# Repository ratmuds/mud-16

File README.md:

# mud-16

a little retro console with a Motorola 68000 and FPGA PPU

# firmware

`ppu.sv` is the Verilog code for the PPU. This is close to what will be the renderer of the game console. `main.cpp` is currently a test bench that gets the display output from the PPU and renders it with Raylib, as well as simulating the CPU bus arbitration and SRAM VRAM access

# features

-   3.5" IPS Display
-   D-pad and ABXY buttons
-   27 MHz FPGA
-   Rechargable Battery
-   512 KB of SRAM

## why

I think that the GameBoy and other retro game console are really cool, and I want to make my own console. But I didn't want to just emulate it, I wanted to use a real retro CPU and make my own PPU (picture processing unit) with a FPGA.

## how

The CPU is the brain pretty much. It handles all the game logic and stuff. It's connected to 512 KB of SRAM which the first part of it is allocated to VRAM. The VRAM is used by the FPGA. The CPU needs to go through level shifters down to 3.3V, and the CPU and FPGA needs to handle bus arbitration properly, otherwise they will fight over the bus and everything will become a mess. The FPGA will request for the bus at the beginning of each frame where they will essentially perform a handshake and the bus will be passed to the FPGA. The FPGA then accesses all the VRAM it needs and then gives back control to the CPU.

The display will be running in 8 bit parallel mode, since SPI is too slow.

## to use

this stuff is WIP

you'll need to flash everything to the FPGA which will load all the necessary data into RAM for the CPU. The Gowin IDE is the app you'll use to flash the Tang Nano.

# Schematic screenshots

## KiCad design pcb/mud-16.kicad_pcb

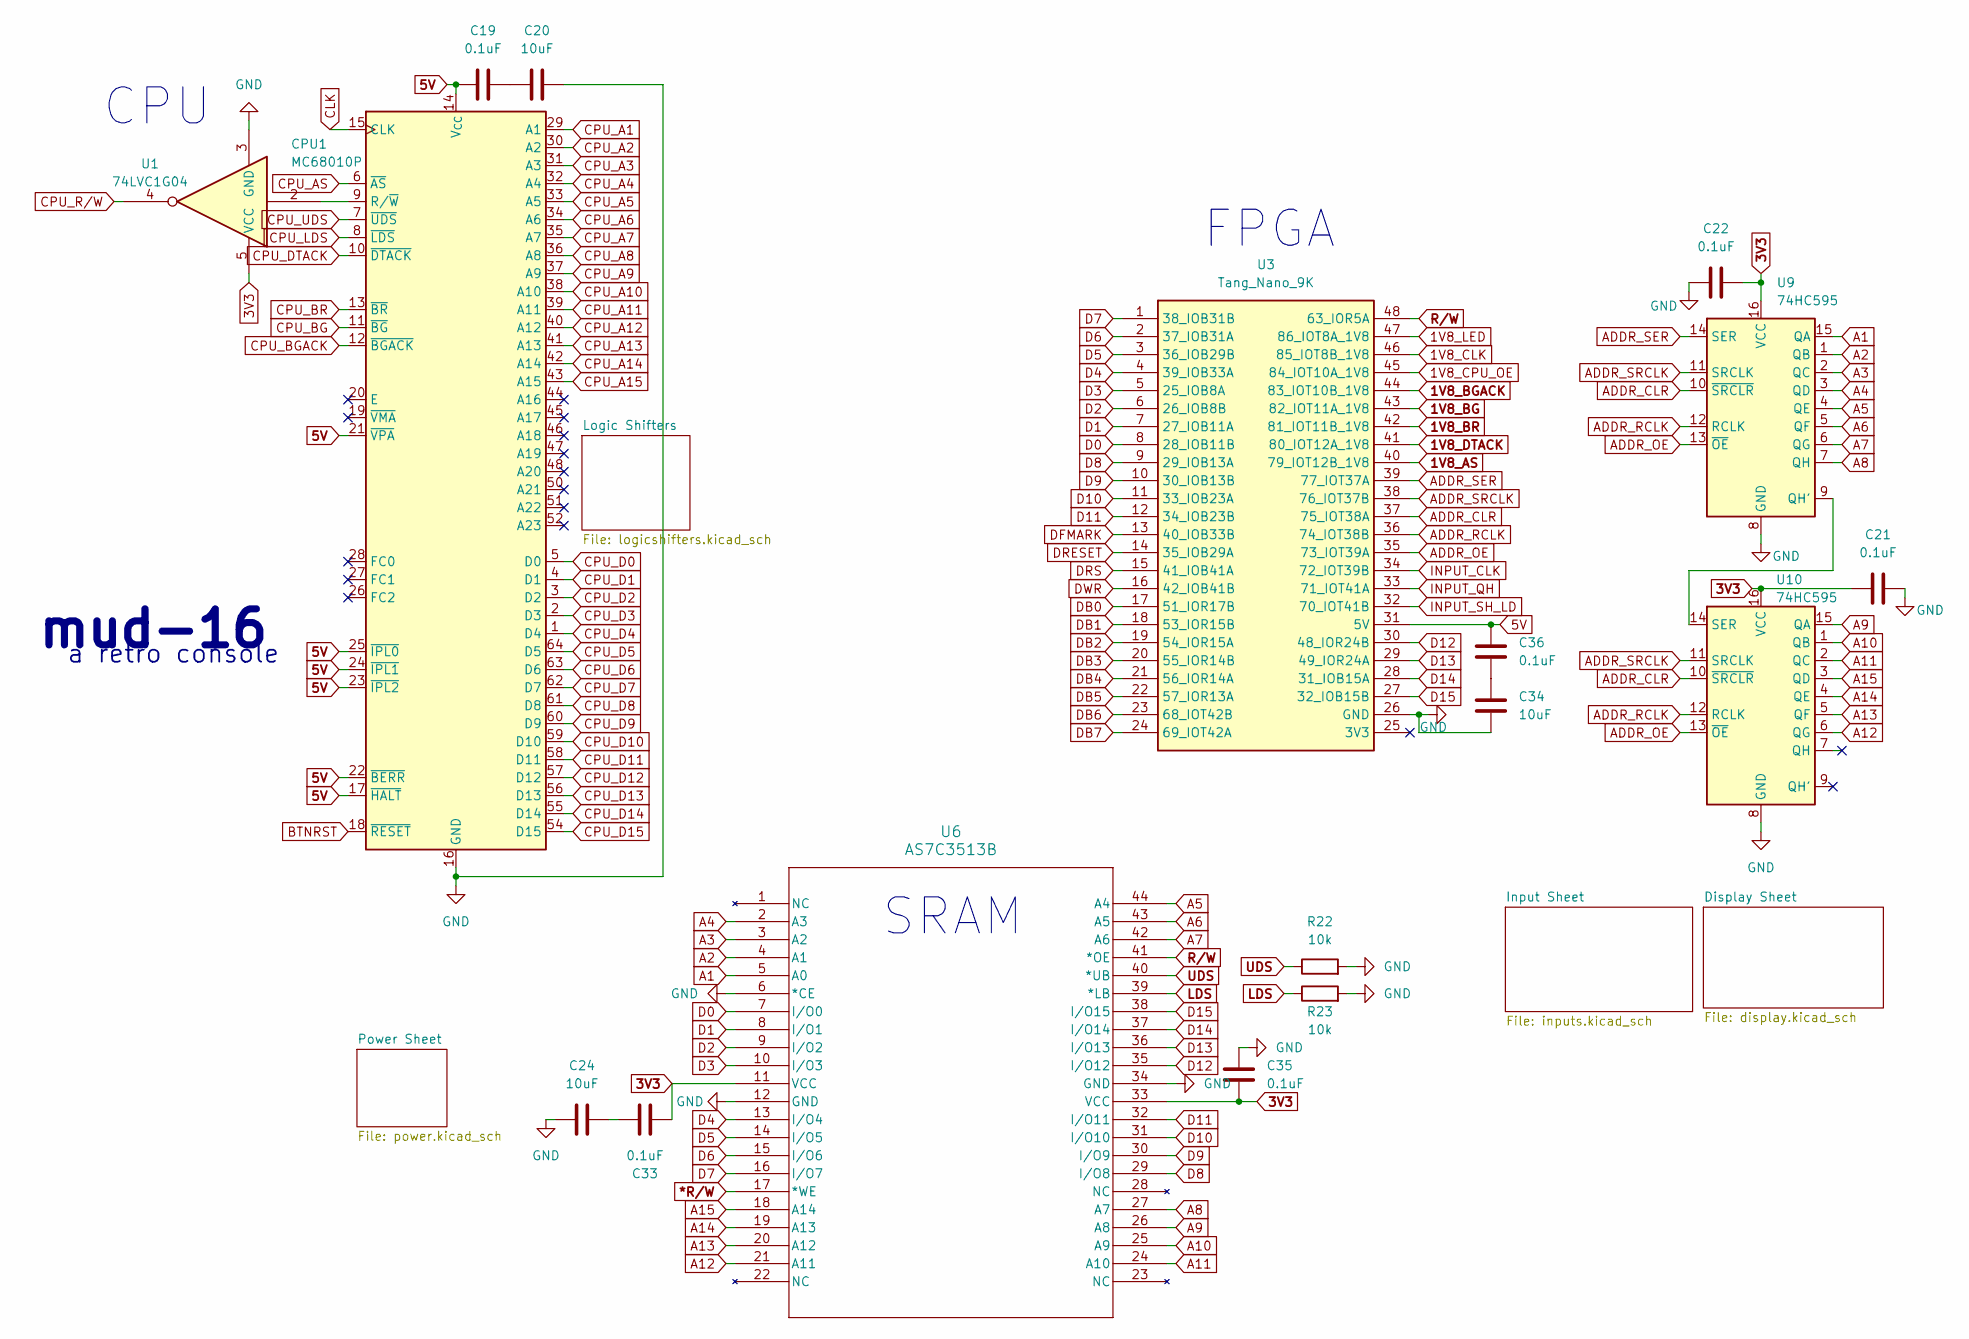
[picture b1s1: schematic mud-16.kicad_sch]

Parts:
C19, C21, C22, C33, C35, C36: 0.1uF; C_0805_2012Metric_Pad1.18x1.45mm_HandSolder
C20, C24, C34: 10uF; C_0805_2012Metric_Pad1.18x1.45mm_HandSolder
CPU1: MC68010P; DIP-64_W22.86mm
R22, R23: 10k; R_0805_2012Metric_Pad1.20x1.40mm_HandSolder
U1: 74LVC1G04; SOT-23-5_HandSoldering
U3: Tang_Nano_9K; DIP-48_TangNano9K
U6: AS7C3513B; TSOP-44_10P2X18P4_ALL
U9, U10: 74HC595; SOIC-16_3.9x9.9mm_P1.27mm

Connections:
1V8_AS: U3.40 (79_IOT12B_1V8); also elsewhere on the board
1V8_BG: U3.43 (82_IOT11A_1V8); also elsewhere on the board
1V8_BGACK: U3.44 (83_IOT10B_1V8); also elsewhere on the board
1V8_BR: U3.42 (81_IOT11B_1V8); also elsewhere on the board
1V8_CLK: U3.46 (85_IOT8B_1V8); also elsewhere on the board
1V8_CPU_OE: U3.45 (84_IOT10A_1V8); also elsewhere on the board
1V8_DTACK: U3.41 (80_IOT12A_1V8); also elsewhere on the board
1V8_LED: U3.47 (86_IOT8A_1V8); also elsewhere on the board
3V3: C21.1, C22.2, C33.1, C35.2, U1.5 (VCC), U6.11 (VCC), U6.33 (VCC), U9.16 (VCC), U10.16 (VCC); also elsewhere on the board
5V: C19.1, C36.1, CPU1.14 (V_{CC}), CPU1.17 (~HALT), CPU1.21 (~VPA), CPU1.22 (~BERR), CPU1.23 (~IPL2), CPU1.24 (~IPL1), CPU1.25 (~IPL0), CPU1.49 (V_{CC}), U3.31 (5V); also elsewhere on the board
*R/W: U6.17 (*WE); also elsewhere on the board
A1: U6.5 (A0), U9.15 (QA); also elsewhere on the board
A2: U6.4 (A1), U9.1 (QB); also elsewhere on the board
A3: U6.3 (A2), U9.2 (QC); also elsewhere on the board
A4: U6.2 (A3), U9.3 (QD); also elsewhere on the board
A5: U6.44 (A4), U9.4 (QE); also elsewhere on the board
A6: U6.43 (A5), U9.5 (QF); also elsewhere on the board
A7: U6.42 (A6), U9.6 (QG); also elsewhere on the board
A8: U6.27 (A7), U9.7 (QH); also elsewhere on the board
A9: U6.26 (A8), U10.15 (QA); also elsewhere on the board
A10: U6.25 (A9), U10.1 (QB); also elsewhere on the board
A11: U6.24 (A10), U10.2 (QC); also elsewhere on the board
A12: U6.21 (A11), U10.6 (QG); also elsewhere on the board
A13: U6.20 (A12), U10.5 (QF); also elsewhere on the board
A14: U6.19 (A13), U10.4 (QE); also elsewhere on the board
A15: U6.18 (A14), U10.3 (QD); also elsewhere on the board
ADDR_CLR: U3.37 (75_IOT38A), U9.10 (~SRCLR), U10.10 (~SRCLR)
ADDR_OE: U3.35 (73_IOT39A), U9.13 (~OE), U10.13 (~OE)
ADDR_RCLK: U3.36 (74_IOT38B), U9.12 (RCLK), U10.12 (RCLK)
ADDR_SER: U3.39 (77_IOT37A), U9.14 (SER)
ADDR_SRCLK: U3.38 (76_IOT37B), U9.11 (SRCLK), U10.11 (SRCLK)
BTNRST: CPU1.18 (~RESET); also elsewhere on the board
CLK: CPU1.15 (CLK); also elsewhere on the board
CPU_A1: CPU1.29 (A1); also elsewhere on the board
CPU_A2: CPU1.30 (A2); also elsewhere on the board
CPU_A3: CPU1.31 (A3); also elsewhere on the board
CPU_A4: CPU1.32 (A4); also elsewhere on the board
CPU_A5: CPU1.33 (A5); also elsewhere on the board
CPU_A6: CPU1.34 (A6); also elsewhere on the board
CPU_A7: CPU1.35 (A7); also elsewhere on the board
CPU_A8: CPU1.36 (A8); also elsewhere on the board
CPU_A9: CPU1.37 (A9); also elsewhere on the board
CPU_A10: CPU1.38 (A10); also elsewhere on the board
CPU_A11: CPU1.39 (A11); also elsewhere on the board
CPU_A12: CPU1.40 (A12); also elsewhere on the board
CPU_A13: CPU1.41 (A13); also elsewhere on the board
CPU_A14: CPU1.42 (A14); also elsewhere on the board
CPU_A15: CPU1.43 (A15); also elsewhere on the board
CPU_AS: CPU1.6 (~AS); also elsewhere on the board
CPU_BG: CPU1.11 (~BG); also elsewhere on the board
CPU_BGACK: CPU1.12 (~BGACK); also elsewhere on the board
CPU_BR: CPU1.13 (~BR); also elsewhere on the board
CPU_D0: CPU1.5 (D0); also elsewhere on the board
CPU_D1: CPU1.4 (D1); also elsewhere on the board
CPU_D2: CPU1.3 (D2); also elsewhere on the board
CPU_D3: CPU1.2 (D3); also elsewhere on the board
CPU_D4: CPU1.1 (D4); also elsewhere on the board
CPU_D5: CPU1.64 (D5); also elsewhere on the board
CPU_D6: CPU1.63 (D6); also elsewhere on the board
CPU_D7: CPU1.62 (D7); also elsewhere on the board
CPU_D8: CPU1.61 (D8); also elsewhere on the board
CPU_D9: CPU1.60 (D9); also elsewhere on the board
CPU_D10: CPU1.59 (D10); also elsewhere on the board
CPU_D11: CPU1.58 (D11); also elsewhere on the board
CPU_D12: CPU1.57 (D12); also elsewhere on the board
CPU_D13: CPU1.56 (D13); also elsewhere on the board
CPU_D14: CPU1.55 (D14); also elsewhere on the board
CPU_D15: CPU1.54 (D15); also elsewhere on the board
CPU_DTACK: CPU1.10 (~DTACK); also elsewhere on the board
CPU_LDS: CPU1.8 (~LDS); also elsewhere on the board
CPU_R/W: U1.4; also elsewhere on the board
CPU_UDS: CPU1.7 (~UDS); also elsewhere on the board
D0: U3.8 (28_IOB11B), U6.7 (I/O0); also elsewhere on the board
D1: U3.7 (27_IOB11A), U6.8 (I/O1); also elsewhere on the board
D2: U3.6 (26_IOB8B), U6.9 (I/O2); also elsewhere on the board
D3: U3.5 (25_IOB8A), U6.10 (I/O3); also elsewhere on the board
D4: U3.4 (39_IOB33A), U6.13 (I/O4); also elsewhere on the board
D5: U3.3 (36_IOB29B), U6.14 (I/O5); also elsewhere on the board
D6: U3.2 (37_IOB31A), U6.15 (I/O6); also elsewhere on the board
D7: U3.1 (38_IOB31B), U6.16 (I/O7); also elsewhere on the board
D8: U3.9 (29_IOB13A), U6.29 (I/O8); also elsewhere on the board
D9: U3.10 (30_IOB13B), U6.30 (I/O9); also elsewhere on the board
D10: U3.11 (33_IOB23A), U6.31 (I/O10); also elsewhere on the board
D11: U3.12 (34_IOB23B), U6.32 (I/O11); also elsewhere on the board
D12: U3.30 (48_IOR24B), U6.35 (I/O12); also elsewhere on the board
D13: U3.29 (49_IOR24A), U6.36 (I/O13); also elsewhere on the board
D14: U3.28 (31_IOB15A), U6.37 (I/O14); also elsewhere on the board
D15: U3.27 (32_IOB15B), U6.38 (I/O15); also elsewhere on the board
DB0: U3.17 (51_IOR17B); also elsewhere on the board
DB1: U3.18 (53_IOR15B); also elsewhere on the board
DB2: U3.19 (54_IOR15A); also elsewhere on the board
DB3: U3.20 (55_IOR14B); also elsewhere on the board
DB4: U3.21 (56_IOR14A); also elsewhere on the board
DB5: U3.22 (57_IOR13A); also elsewhere on the board
DB6: U3.23 (68_IOT42B); also elsewhere on the board
DB7: U3.24 (69_IOT42A); also elsewhere on the board
DFMARK: U3.13 (40_IOB33B); also elsewhere on the board
DRESET: U3.14 (35_IOB29A); also elsewhere on the board
DRS: U3.15 (41_IOB41A); also elsewhere on the board
DWR: U3.16 (42_IOB41B); also elsewhere on the board
GND: C20.2, C21.2, C22.1, C24.1, C34.2, C35.1, CPU1.16 (GND), CPU1.53 (GND), R22.2, R23.2, U1.3 (GND), U3.26 (GND), U6.6 (*CE), U6.12 (GND), U6.34 (GND), U9.8 (GND), U10.8 (GND); also elsewhere on the board
INPUT_CLK: U3.34 (72_IOT39B); also elsewhere on the board
INPUT_QH: U3.33 (71_IOT41A); also elsewhere on the board
INPUT_SH_LD: U3.32 (70_IOT41B); also elsewhere on the board
LDS: R23.1, U6.39 (*LB); also elsewhere on the board
unnamed: C19.2, C20.1
unnamed: C24.2, C33.2
unnamed: C34.1, C36.2
unnamed: CPU1.9 (R/~W), U1.2
unnamed: U9.9 (QH'), U10.14 (SER)
R/W: U3.48 (63_IOR5A), U6.41 (*OE); also elsewhere on the board
UDS: R22.1, U6.40 (*UB); also elsewhere on the board

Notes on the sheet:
mud-16
SRAM
FPGA
a retro console
CPU

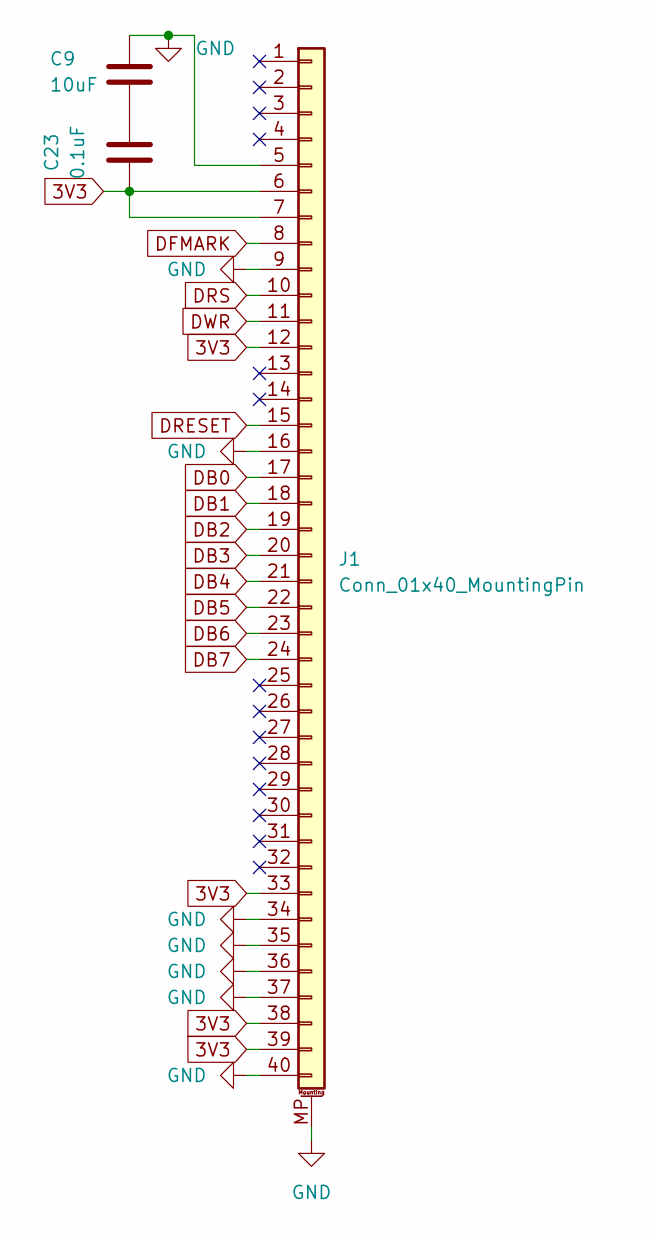
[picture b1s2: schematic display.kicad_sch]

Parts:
C9: 10uF; C_0805_2012Metric_Pad1.18x1.45mm_HandSolder
C23: 0.1uF; C_0805_2012Metric_Pad1.18x1.45mm_HandSolder
J1: Conn_01x40_MountingPin; Amphenol_F32R-1A7x1-11040_1x40-1MP_P0.5mm_Horizontal

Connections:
3V3: C23.1, J1.6, J1.7, J1.12, J1.33, J1.38, J1.39; also elsewhere on the board
DB0: J1.17; also elsewhere on the board
DB1: J1.18; also elsewhere on the board
DB2: J1.19; also elsewhere on the board
DB3: J1.20; also elsewhere on the board
DB4: J1.21; also elsewhere on the board
DB5: J1.22; also elsewhere on the board
DB6: J1.23; also elsewhere on the board
DB7: J1.24; also elsewhere on the board
DFMARK: J1.8; also elsewhere on the board
DRESET: J1.15; also elsewhere on the board
DRS: J1.10; also elsewhere on the board
DWR: J1.11; also elsewhere on the board
GND: C9.1, J1.5, J1.9, J1.16, J1.34, J1.35, J1.36, J1.37, J1.40, J1.MP (MountPin); also elsewhere on the board
unnamed: C9.2, C23.2

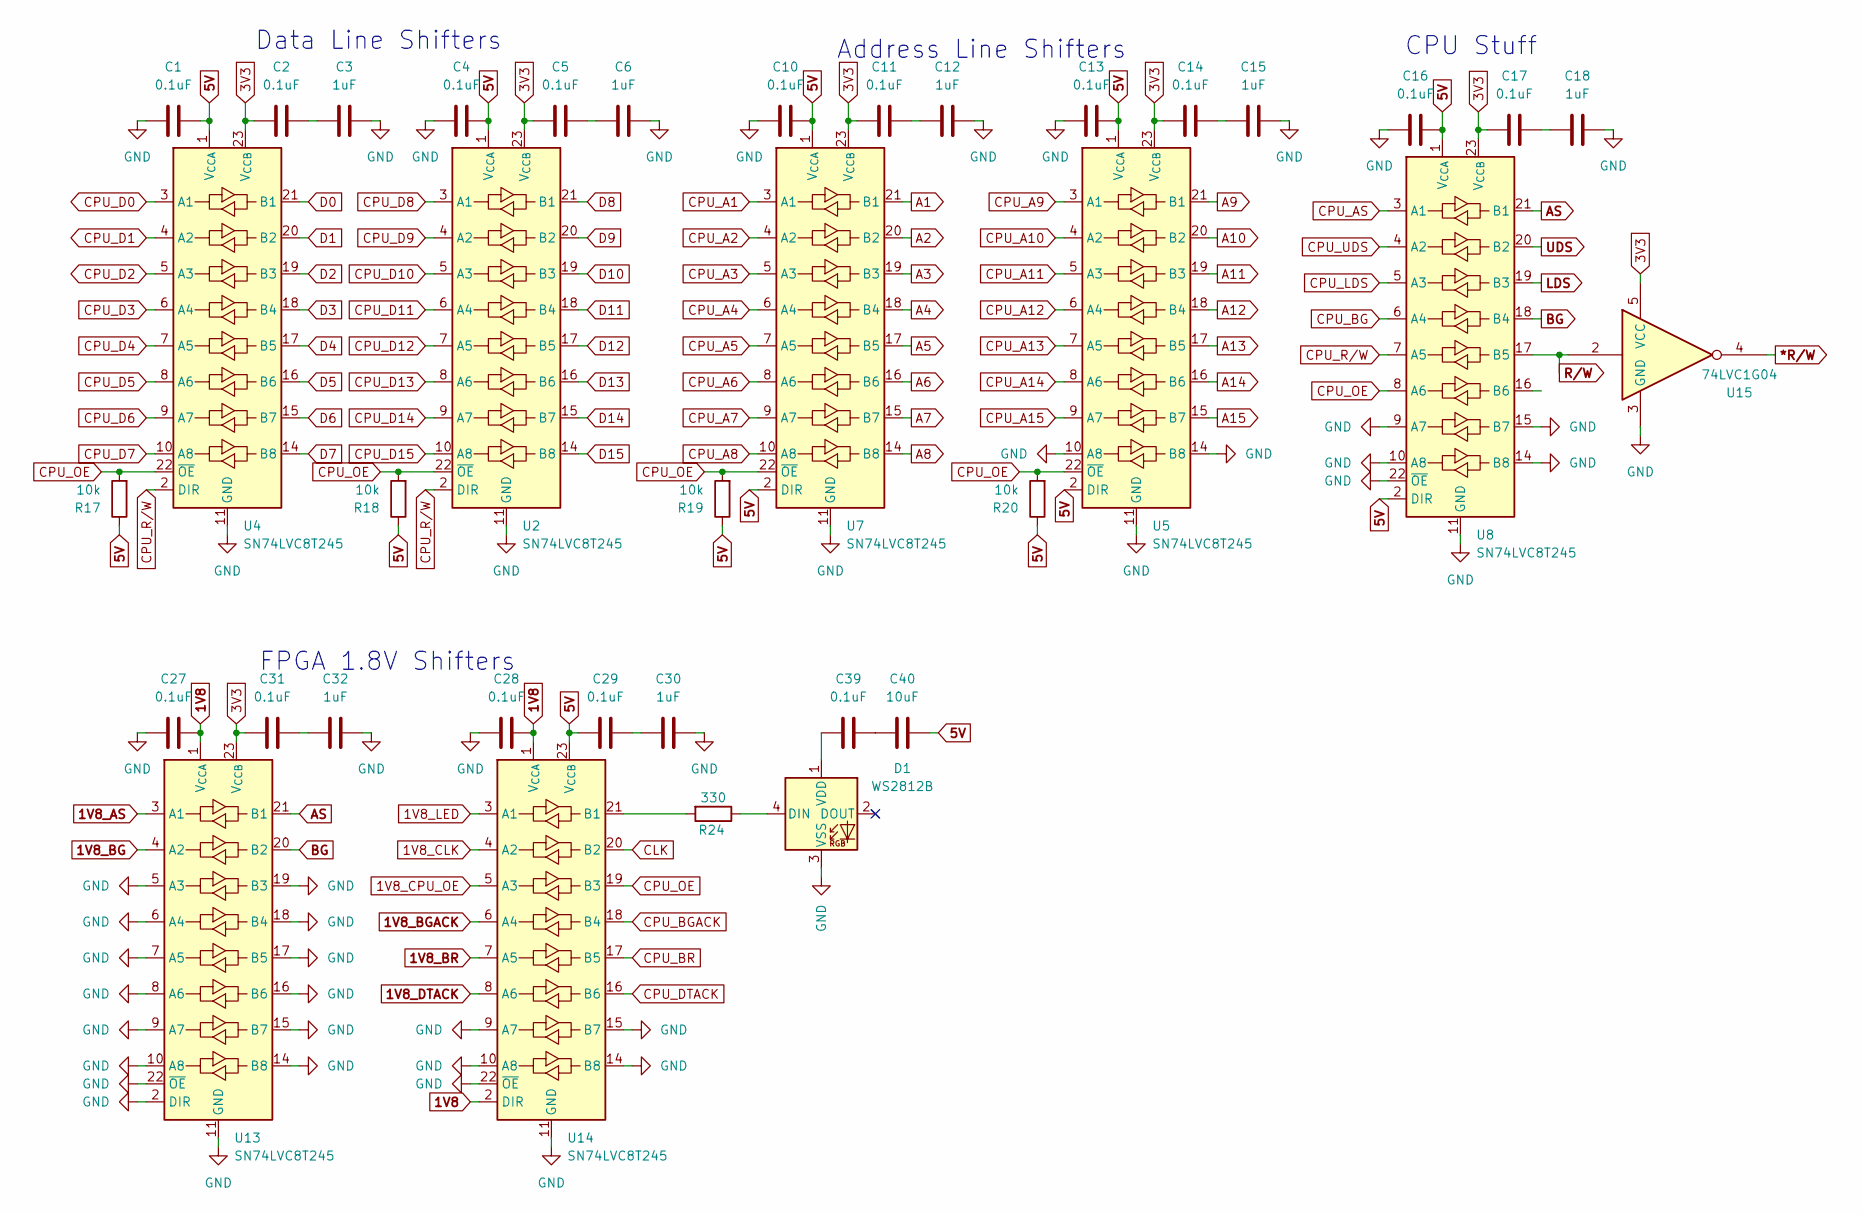
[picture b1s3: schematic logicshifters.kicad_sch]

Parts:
C1, C2, C4, C5, C10, C11, C13, C14, C16, C17, C27, C28, C29, C31, C39: 0.1uF; C_0805_2012Metric_Pad1.18x1.45mm_HandSolder
C3, C6, C12, C15, C18, C30, C32: 1uF; C_0805_2012Metric_Pad1.18x1.45mm_HandSolder
C40: 10uF; C_0805_2012Metric_Pad1.18x1.45mm_HandSolder
D1: WS2812B; LED_WS2812B_PLCC4_5.0x5.0mm_P3.2mm
R17, R18, R19, R20: 10k; R_0805_2012Metric_Pad1.20x1.40mm_HandSolder
R24: 330; R_0805_2012Metric_Pad1.20x1.40mm_HandSolder
U2, U4, U5, U7, U8, U13, U14: SN74LVC8T245; TSSOP-24_4.4x7.8mm_P0.65mm
U15: 74LVC1G04; SOT-23-5_HandSoldering

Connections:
1V8: C27.2, C28.2, U13.1 (V_{CCA}), U14.1 (V_{CCA}), U14.2 (DIR); also elsewhere on the board
1V8_AS: U13.3 (A1); also elsewhere on the board
1V8_BG: U13.4 (A2); also elsewhere on the board
1V8_BGACK: U14.6 (A4); also elsewhere on the board
1V8_BR: U14.7 (A5); also elsewhere on the board
1V8_CLK: U14.4 (A2); also elsewhere on the board
1V8_CPU_OE: U14.5 (A3); also elsewhere on the board
1V8_DTACK: U14.8 (A6); also elsewhere on the board
1V8_LED: U14.3 (A1); also elsewhere on the board
3V3: C2.1, C5.1, C11.1, C14.1, C17.1, C31.1, U2.23 (V_{CCB}), U2.24 (V_{CCB}), U4.23 (V_{CCB}), U4.24 (V_{CCB}), U5.23 (V_{CCB}), U5.24 (V_{CCB}), U7.23 (V_{CCB}), U7.24 (V_{CCB}), U8.23 (V_{CCB}), U8.24 (V_{CCB}), U13.23 (V_{CCB}), U13.24 (V_{CCB}), U15.5 (VCC); also elsewhere on the board
5V: C1.2, C4.2, C10.2, C13.2, C16.2, C29.1, C40.2, R17.1, R18.1, R19.1, R20.1, U2.1 (V_{CCA}), U4.1 (V_{CCA}), U5.1 (V_{CCA}), U5.2 (DIR), U7.1 (V_{CCA}), U7.2 (DIR), U8.1 (V_{CCA}), U8.2 (DIR), U14.23 (V_{CCB}), U14.24 (V_{CCB}); also elsewhere on the board
*R/W: U15.4; also elsewhere on the board
A1: U7.21 (B1); also elsewhere on the board
A2: U7.20 (B2); also elsewhere on the board
A3: U7.19 (B3); also elsewhere on the board
A4: U7.18 (B4); also elsewhere on the board
A5: U7.17 (B5); also elsewhere on the board
A6: U7.16 (B6); also elsewhere on the board
A7: U7.15 (B7); also elsewhere on the board
A8: U7.14 (B8); also elsewhere on the board
A9: U5.21 (B1); also elsewhere on the board
A10: U5.20 (B2); also elsewhere on the board
A11: U5.19 (B3); also elsewhere on the board
A12: U5.18 (B4); also elsewhere on the board
A13: U5.17 (B5); also elsewhere on the board
A14: U5.16 (B6); also elsewhere on the board
A15: U5.15 (B7); also elsewhere on the board
AS: U8.21 (B1), U13.21 (B1)
BG: U8.18 (B4), U13.20 (B2)
CLK: U14.20 (B2); also elsewhere on the board
CPU_A1: U7.3 (A1); also elsewhere on the board
CPU_A2: U7.4 (A2); also elsewhere on the board
CPU_A3: U7.5 (A3); also elsewhere on the board
CPU_A4: U7.6 (A4); also elsewhere on the board
CPU_A5: U7.7 (A5); also elsewhere on the board
CPU_A6: U7.8 (A6); also elsewhere on the board
CPU_A7: U7.9 (A7); also elsewhere on the board
CPU_A8: U7.10 (A8); also elsewhere on the board
CPU_A9: U5.3 (A1); also elsewhere on the board
CPU_A10: U5.4 (A2); also elsewhere on the board
CPU_A11: U5.5 (A3); also elsewhere on the board
CPU_A12: U5.6 (A4); also elsewhere on the board
CPU_A13: U5.7 (A5); also elsewhere on the board
CPU_A14: U5.8 (A6); also elsewhere on the board
CPU_A15: U5.9 (A7); also elsewhere on the board
CPU_AS: U8.3 (A1); also elsewhere on the board
CPU_BG: U8.6 (A4); also elsewhere on the board
CPU_BGACK: U14.18 (B4); also elsewhere on the board
CPU_BR: U14.17 (B5); also elsewhere on the board
CPU_D0: U4.3 (A1); also elsewhere on the board
CPU_D1: U4.4 (A2); also elsewhere on the board
CPU_D2: U4.5 (A3); also elsewhere on the board
CPU_D3: U4.6 (A4); also elsewhere on the board
CPU_D4: U4.7 (A5); also elsewhere on the board
CPU_D5: U4.8 (A6); also elsewhere on the board
CPU_D6: U4.9 (A7); also elsewhere on the board
CPU_D7: U4.10 (A8); also elsewhere on the board
CPU_D8: U2.3 (A1); also elsewhere on the board
CPU_D9: U2.4 (A2); also elsewhere on the board
CPU_D10: U2.5 (A3); also elsewhere on the board
CPU_D11: U2.6 (A4); also elsewhere on the board
CPU_D12: U2.7 (A5); also elsewhere on the board
CPU_D13: U2.8 (A6); also elsewhere on the board
CPU_D14: U2.9 (A7); also elsewhere on the board
CPU_D15: U2.10 (A8); also elsewhere on the board
CPU_DTACK: U14.16 (B6); also elsewhere on the board
CPU_LDS: U8.5 (A3); also elsewhere on the board
CPU_OE: R17.2, R18.2, R19.2, R20.2, U2.22 (~OE), U4.22 (~OE), U5.22 (~OE), U7.22 (~OE), U8.8 (A6), U14.19 (B3)
CPU_R/W: U2.2 (DIR), U4.2 (DIR), U8.7 (A5); also elsewhere on the board
CPU_UDS: U8.4 (A2); also elsewhere on the board
D0: U4.21 (B1); also elsewhere on the board
D1: U4.20 (B2); also elsewhere on the board
D2: U4.19 (B3); also elsewhere on the board
D3: U4.18 (B4); also elsewhere on the board
D4: U4.17 (B5); also elsewhere on the board
D5: U4.16 (B6); also elsewhere on the board
D6: U4.15 (B7); also elsewhere on the board
D7: U4.14 (B8); also elsewhere on the board
D8: U2.21 (B1); also elsewhere on the board
D9: U2.20 (B2); also elsewhere on the board
D10: U2.19 (B3); also elsewhere on the board
D11: U2.18 (B4); also elsewhere on the board
D12: U2.17 (B5); also elsewhere on the board
D13: U2.16 (B6); also elsewhere on the board
D14: U2.15 (B7); also elsewhere on the board
D15: U2.14 (B8); also elsewhere on the board
GND: C1.1, C3.2, C4.1, C6.2, C10.1, C12.2, C13.1, C15.2, C16.1, C18.2, C27.1, C28.1, C30.2, C32.2, D1.3 (VSS), U2.11 (GND), U2.12 (GND), U2.13 (GND), U4.11 (GND), U4.12 (GND), U4.13 (GND), U5.10 (A8), U5.11 (GND), U5.12 (GND), U5.13 (GND), U5.14 (B8), U7.11 (GND), U7.12 (GND), U7.13 (GND), U8.9 (A7), U8.10 (A8), U8.11 (GND), U8.12 (GND), U8.13 (GND), U8.14 (B8), U8.15 (B7), U8.22 (~OE), U13.2 (DIR), U13.5 (A3), U13.6 (A4), U13.7 (A5), U13.8 (A6), U13.9 (A7), U13.10 (A8), U13.11 (GND), U13.12 (GND), U13.13 (GND), U13.14 (B8), U13.15 (B7), U13.16 (B6), U13.17 (B5), U13.18 (B4), U13.19 (B3), U13.22 (~OE), U14.9 (A7), U14.10 (A8), U14.11 (GND), U14.12 (GND), U14.13 (GND), U14.14 (B8), U14.15 (B7), U14.22 (~OE), U15.3 (GND); also elsewhere on the board
LDS: U8.19 (B3); also elsewhere on the board
unnamed: C2.2, C3.1
unnamed: C5.2, C6.1
unnamed: C11.2, C12.1
unnamed: C14.2, C15.1
unnamed: C17.2, C18.1
unnamed: C29.2, C30.1
unnamed: C31.2, C32.1
unnamed: C39.2, C40.1
unnamed: D1.4 (DIN), R24.1
unnamed: C39.1, D1.1 (VDD)
unnamed: R24.2, U14.21 (B1)
R/W: U8.17 (B5), U15.2; also elsewhere on the board
UDS: U8.20 (B2); also elsewhere on the board

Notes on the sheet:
CPU Stuff
Data Line Shifters
FPGA 1.8V Shifters
Address Line Shifters

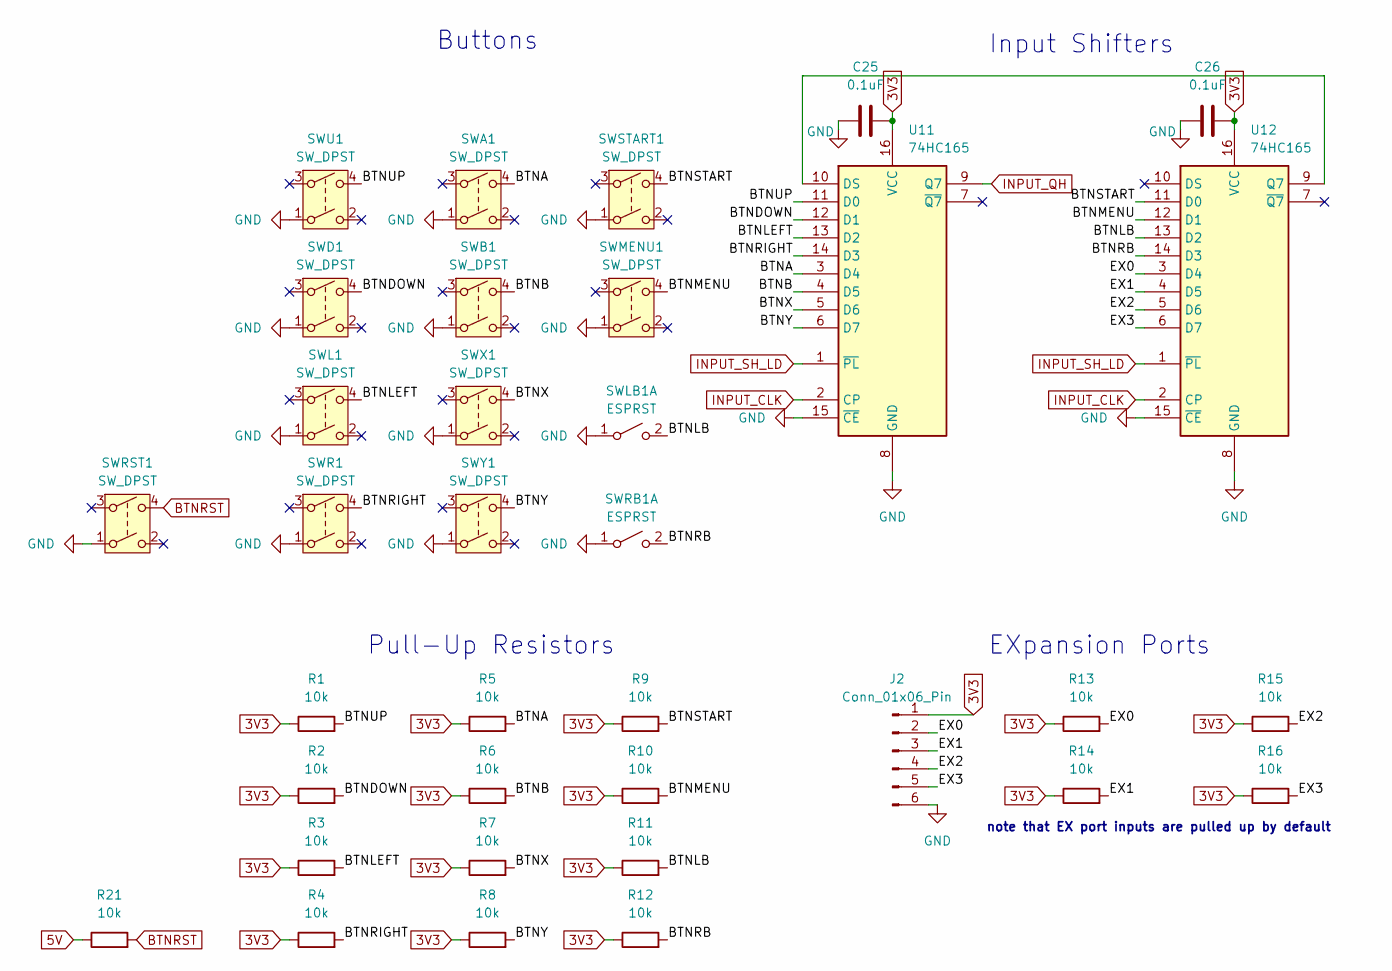
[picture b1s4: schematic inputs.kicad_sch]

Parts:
C25, C26: 0.1uF; C_0805_2012Metric_Pad1.18x1.45mm_HandSolder
J2: Conn_01x06_Pin; PinSocket_1x06_P2.54mm_Vertical
R1, R2, R3, R4, R5, R6, R7, R8, R9, R10, R11, R12, R13, R14, R15, R16, R21: 10k; R_0805_2012Metric_Pad1.20x1.40mm_HandSolder
SWA1: SW_DPST; SW_PUSH_6mm
SWB1: SW_DPST; SW_PUSH_6mm
SWD1: SW_DPST; SW_PUSH_6mm
SWL1: SW_DPST; SW_PUSH_6mm
SWLB1: ESPRST; SW_SIDE_PUSH_3x6mm
SWMENU1: SW_DPST; SW_PUSH_6mm
SWR1: SW_DPST; SW_PUSH_6mm
SWRB1: ESPRST; SW_SIDE_PUSH_3x6mm
SWRST1: SW_DPST; SW_PUSH_6mm
SWSTART1: SW_DPST; SW_PUSH_6mm
SWU1: SW_DPST; SW_PUSH_6mm
SWX1: SW_DPST; SW_PUSH_6mm
SWY1: SW_DPST; SW_PUSH_6mm
U11, U12: 74HC165; DIP-16_W7.62mm

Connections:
3V3: C25.2, C26.2, J2.1, R1.1, R2.1, R3.1, R4.1, R5.1, R6.1, R7.1, R8.1, R9.1, R10.1, R11.1, R12.1, R13.1, R14.1, R15.1, R16.1, U11.16 (VCC), U12.16 (VCC); also elsewhere on the board
5V: R21.1; also elsewhere on the board
/Input Sheet/BTNA: R5.2, SWA1.4, U11.3 (D4)
/Input Sheet/BTNB: R6.2, SWB1.4, U11.4 (D5)
/Input Sheet/BTNDOWN: R2.2, SWD1.4, U11.12 (D1)
/Input Sheet/BTNLB: R11.2, SWLB1.2 (B), U12.13 (D2)
/Input Sheet/BTNLEFT: R3.2, SWL1.4, U11.13 (D2)
/Input Sheet/BTNMENU: R10.2, SWMENU1.4, U12.12 (D1)
/Input Sheet/BTNRB: R12.2, SWRB1.2 (B), U12.14 (D3)
/Input Sheet/BTNRIGHT: R4.2, SWR1.4, U11.14 (D3)
/Input Sheet/BTNSTART: R9.2, SWSTART1.4, U12.11 (D0)
/Input Sheet/BTNUP: R1.2, SWU1.4, U11.11 (D0)
/Input Sheet/BTNX: R7.2, SWX1.4, U11.5 (D6)
/Input Sheet/BTNY: R8.2, SWY1.4, U11.6 (D7)
/Input Sheet/EX0: J2.2, R13.2, U12.3 (D4)
/Input Sheet/EX1: J2.3, R14.2, U12.4 (D5)
/Input Sheet/EX2: J2.4, R15.2, U12.5 (D6)
/Input Sheet/EX3: J2.5, R16.2, U12.6 (D7)
BTNRST: R21.2, SWRST1.4; also elsewhere on the board
GND: C25.1, C26.1, J2.6, SWA1.1, SWB1.1, SWD1.1, SWL1.1, SWLB1.1 (A), SWMENU1.1, SWR1.1, SWRB1.1 (A), SWRST1.1, SWSTART1.1, SWU1.1, SWX1.1, SWY1.1, U11.8 (GND), U11.15 (~CE), U12.8 (GND), U12.15 (~CE); also elsewhere on the board
INPUT_CLK: U11.2 (CP), U12.2 (CP); also elsewhere on the board
INPUT_QH: U11.9 (Q7); also elsewhere on the board
INPUT_SH_LD: U11.1 (~PL), U12.1 (~PL); also elsewhere on the board
unnamed: U11.10 (DS), U12.9 (Q7)

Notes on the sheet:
Pull-Up Resistors
EXpansion Ports
note that EX port inputs are pulled up by default
Buttons
Input Shifters

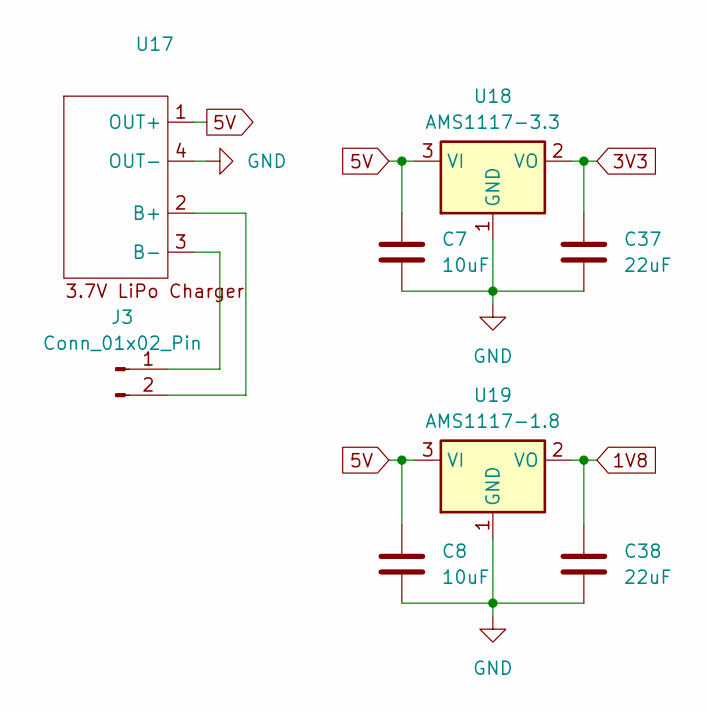
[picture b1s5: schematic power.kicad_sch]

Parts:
C7, C8: 10uF; C_0805_2012Metric_Pad1.18x1.45mm_HandSolder
C37, C38: 22uF; C_0805_2012Metric_Pad1.18x1.45mm_HandSolder
J3: Conn_01x02_Pin; JST_PH_S2B-PH-K_1x02_P2.00mm_Horizontal
U17: 3.7V_LiPo_Charging_Board
U18: AMS1117-3.3; SOT-223-3_TabPin2
U19: AMS1117-1.8; SOT-223-3_TabPin2

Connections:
1V8: C38.1, U19.2 (VO); also elsewhere on the board
3V3: C37.1, U18.2 (VO); also elsewhere on the board
5V: C7.1, C8.1, U17.1 (OUT+), U18.3 (VI), U19.3 (VI); also elsewhere on the board
GND: C7.2, C8.2, C37.2, C38.2, U17.4 (OUT-), U18.1 (GND), U19.1 (GND); also elsewhere on the board
unnamed: J3.1, U17.3 (B-)
unnamed: J3.2, U17.2 (B+)

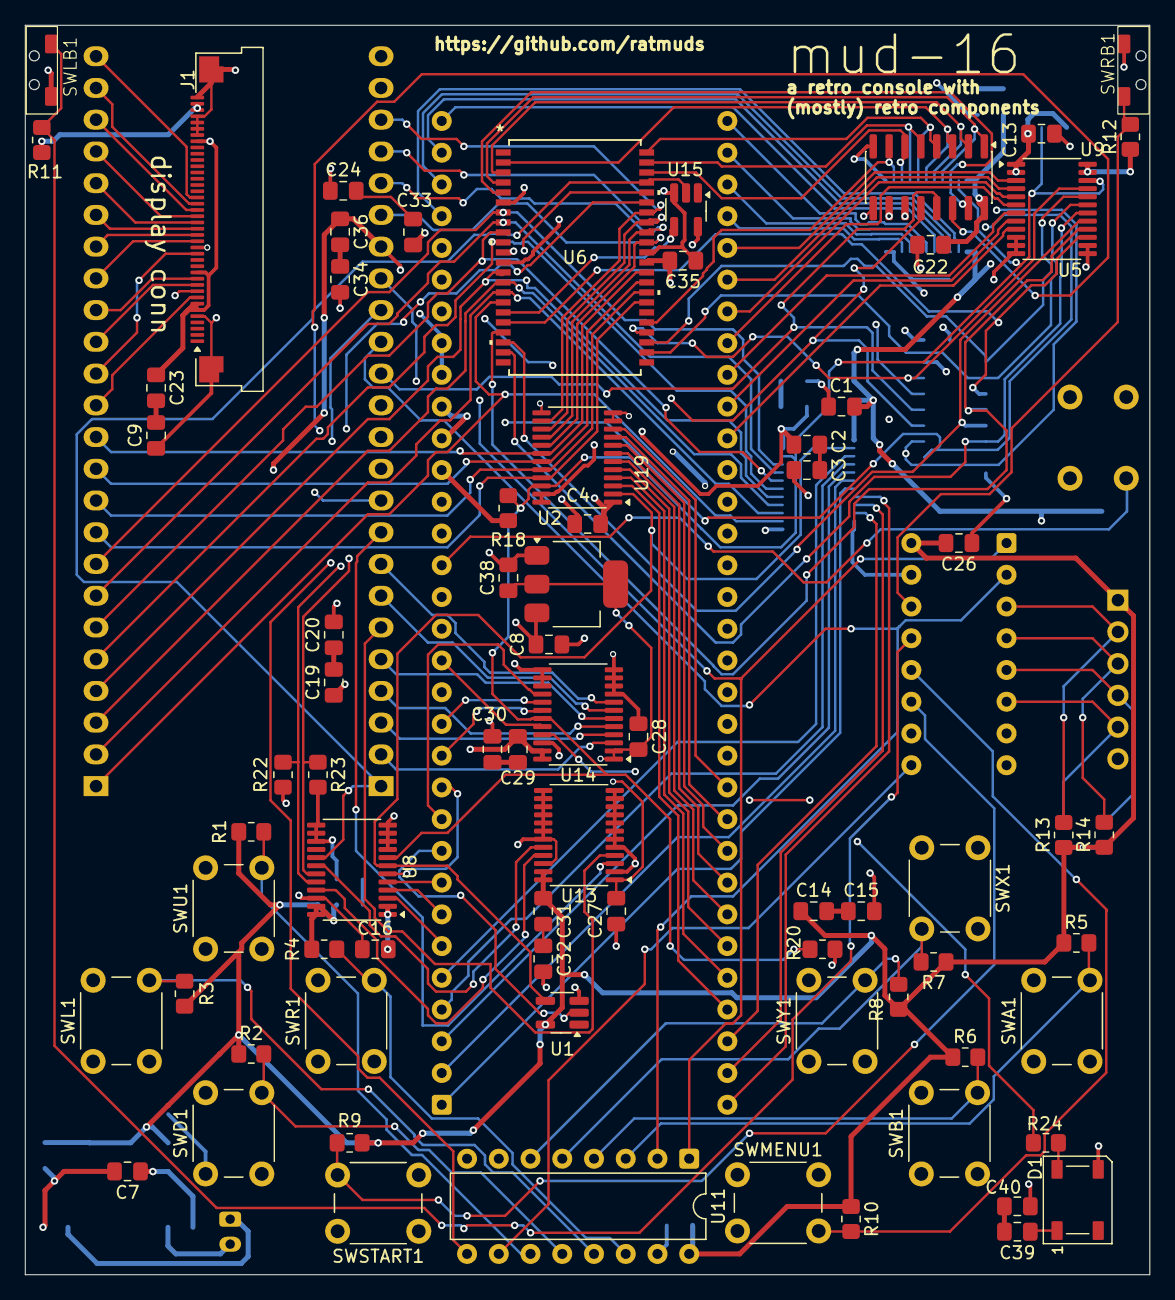
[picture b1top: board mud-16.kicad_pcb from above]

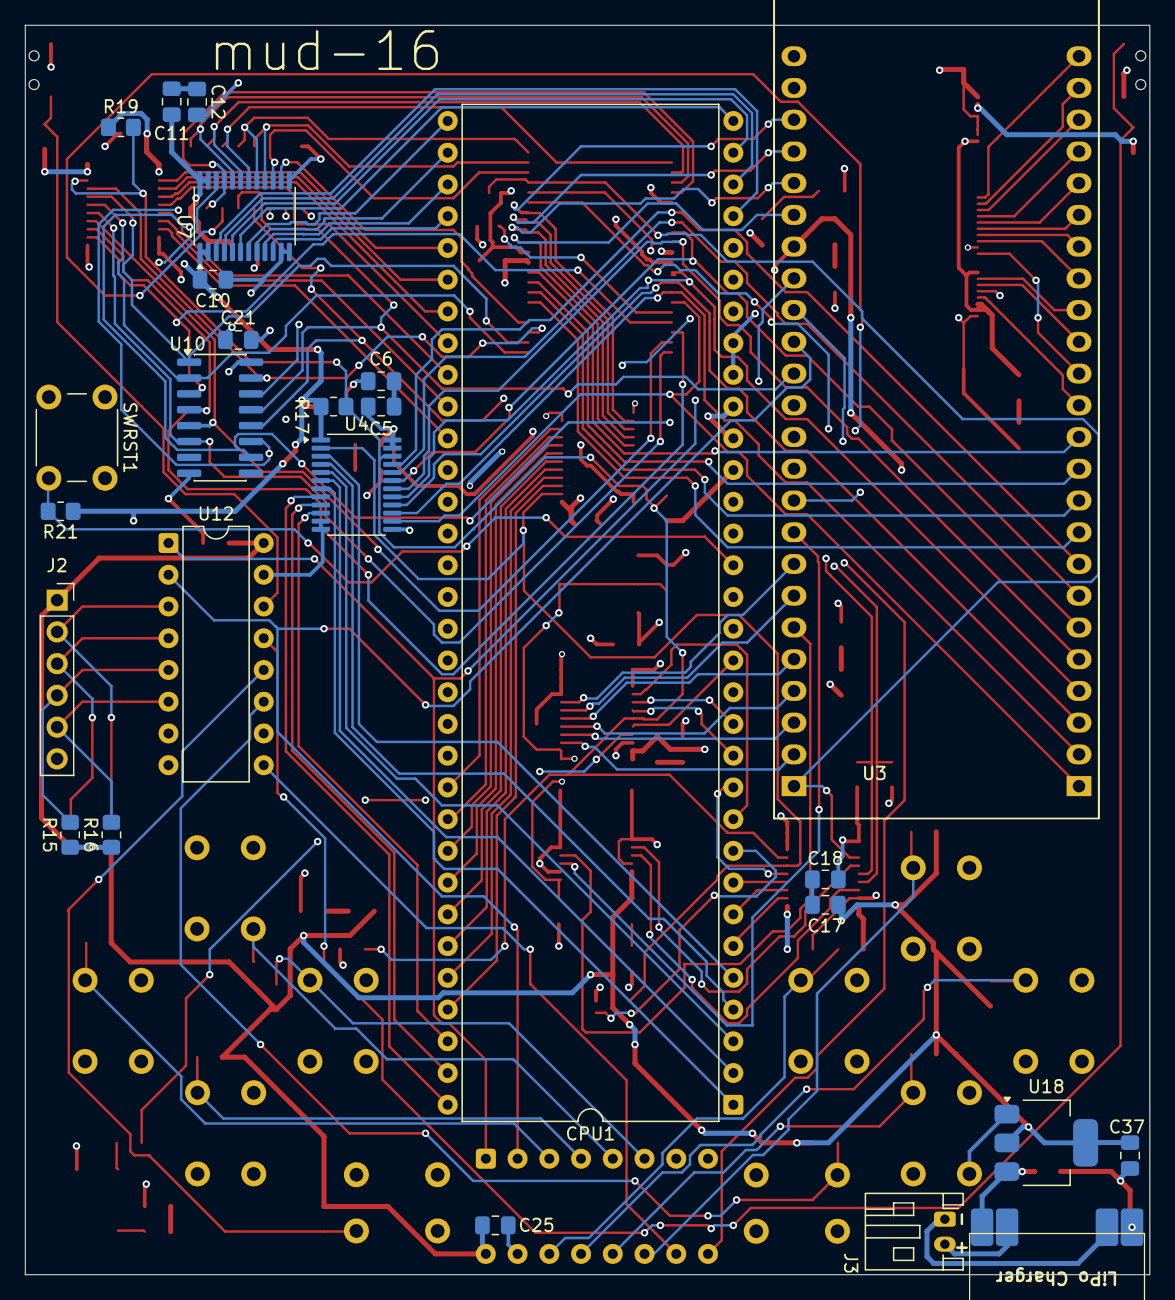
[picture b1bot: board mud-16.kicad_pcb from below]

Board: 4 copper layers, 90.0 x 99.9 mm, 100 parts (26 on the bottom side), 147 nets.

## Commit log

2025-12-02 basic PPU stuff
2025-12-04 Renders, but broken for now. Probably because some sync signals are needed. Also high CPU usage, need to fix that.
2025-12-04 Fix rendering bug
2025-12-04 background
2025-12-05 UI layer
2025-12-07 load video data from simulated RAM
2025-12-09 feat: Implement scrolling and create grant proposal
    This commit introduces two main changes:
    1. **PPU Scrolling:** Implemented background scrolling in the PPU by adding `scroll_x` and `scroll_y` registers. This allows the background to be moved, a fundamental feature for many retro games.
    2. **Grant Proposal:** Created a `grant_proposal.md` file to outline the project's goals, current status, and the work that needs to be completed to apply for a hardware grant. This file will serve a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
2025-12-09 bug fixes
2025-12-11 add PCB for now (not finished)
2025-12-13 Placed components on PCB
2025-12-14 routing pcb
2025-12-15 almost done routing
2025-12-15 finish routing
2025-12-16 readme
    Added features, purpose, and usage sections to README.
2025-12-16 extra files
2025-12-16 more images
    Added a new image to the README and updated the table.
2025-12-17 reorganize
2025-12-17 move readme back
2025-12-18 remove fusion file
2025-12-18 update BOM
2025-12-18 Add schematic screenshots section to README
    Added schematic screenshots to the README.
2025-12-23 edit BOM
2025-12-23 changes to BOM
2025-12-24 update links
2025-12-28 Initial plan
2025-12-28 Remove logic analyzer and helping hands from BOM.csv and README.md
2026-01-02 Replace PCB + PCBA with separate PCB and PCB Assembly entries
2026-01-02 Revise PCB description in the README
    Updated PCB entry to reflect changes in description.
2026-01-02 Add 11 new PCBA parts to BOM.csv and README.md
2026-03-31 Remove old BOM
